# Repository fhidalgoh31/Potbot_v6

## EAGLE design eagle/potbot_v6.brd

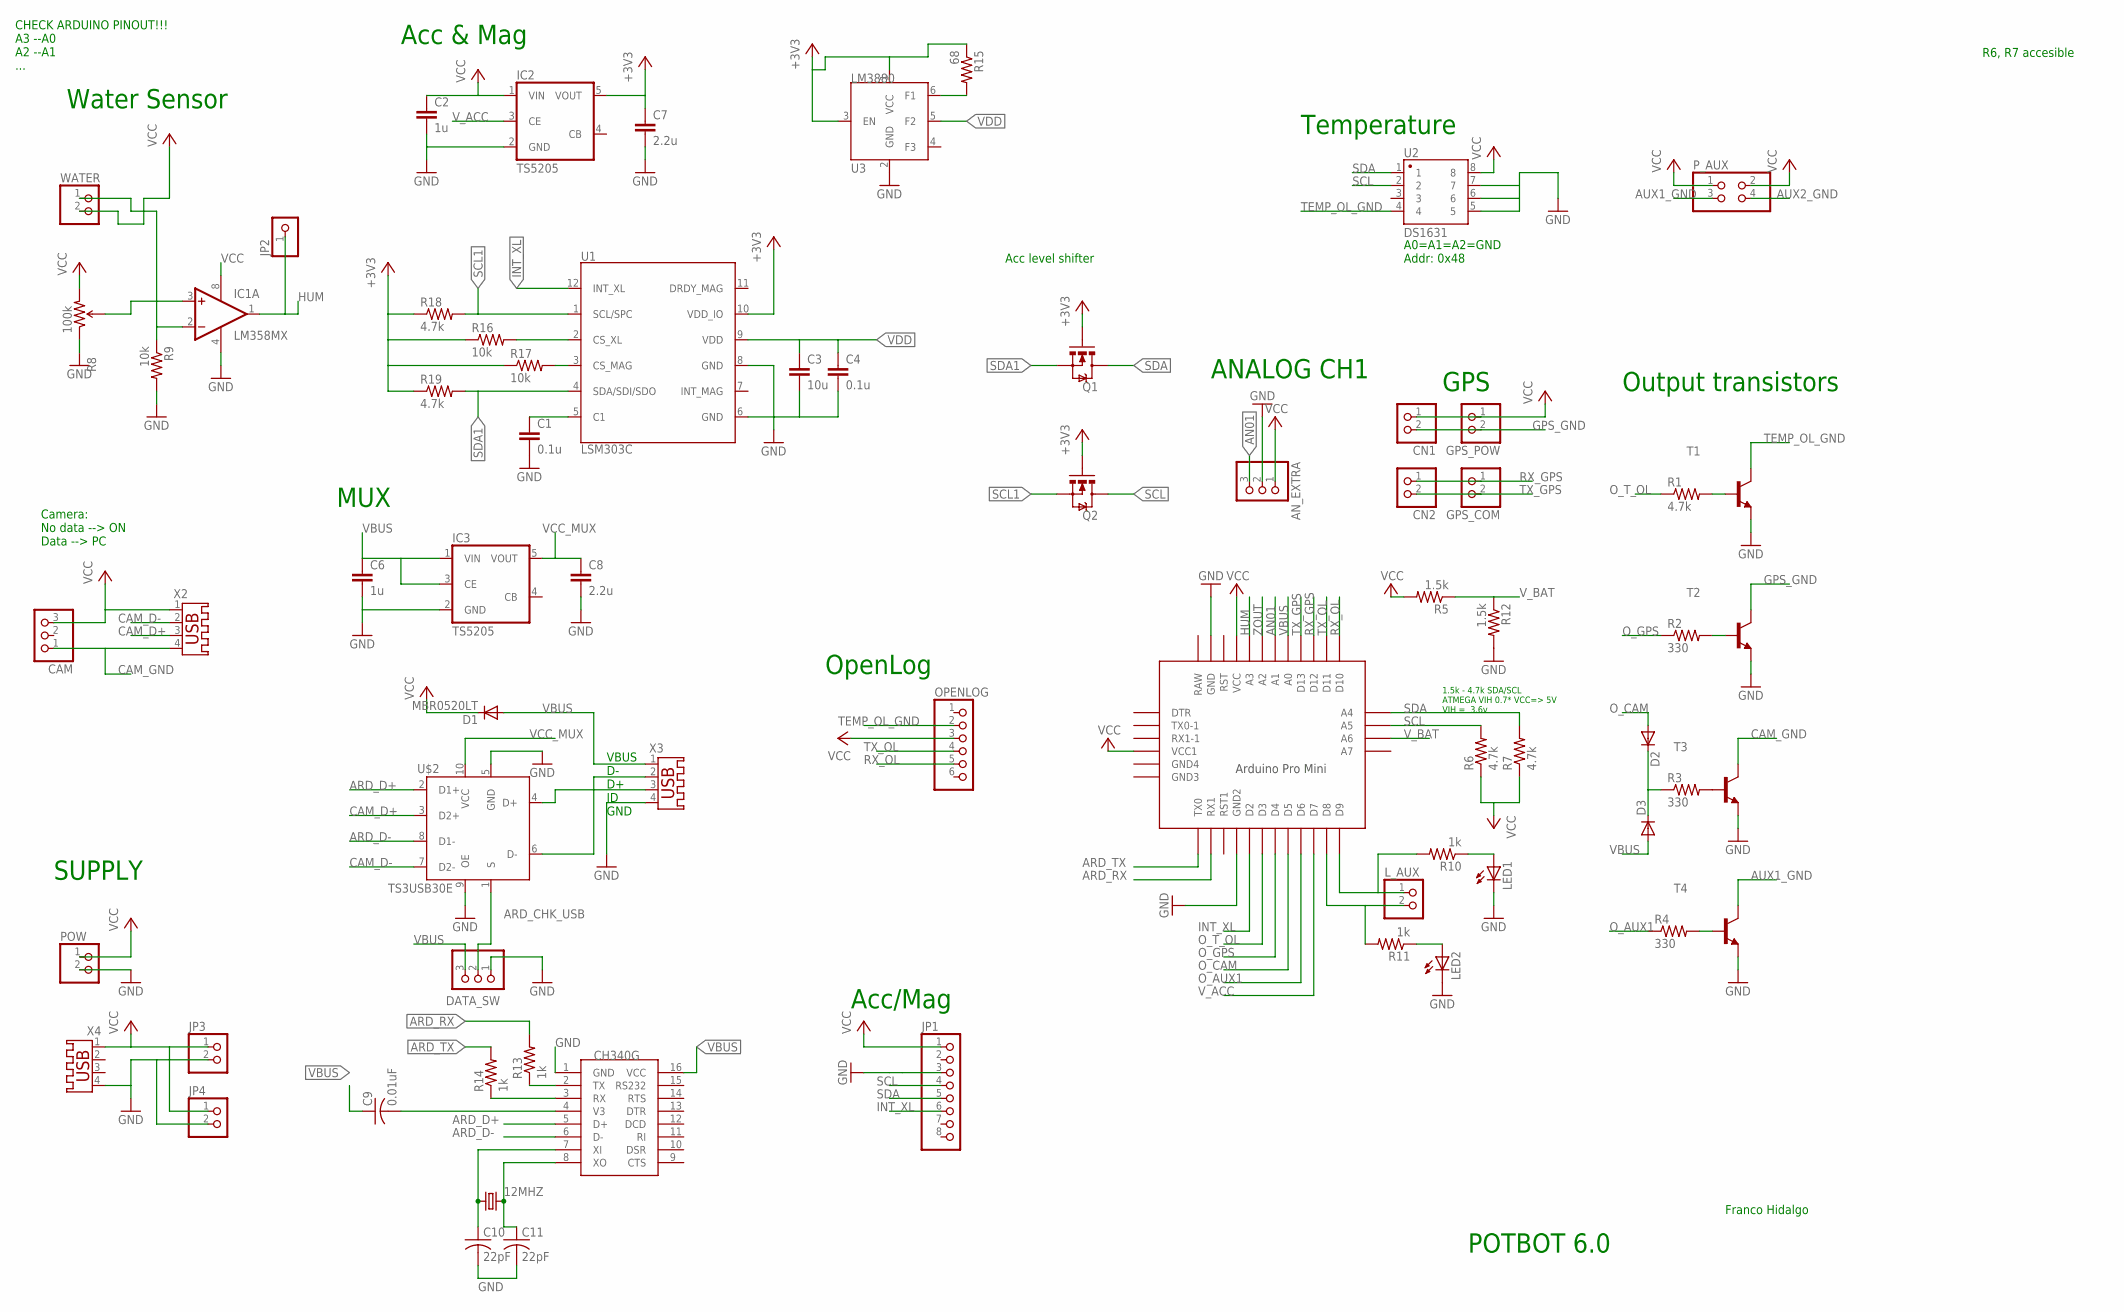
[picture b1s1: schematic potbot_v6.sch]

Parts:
12MHZ: CRYSTALSM49; SM49
AN_EXTRA: PINHD-1X3; 1X03
ARDUINO: PRO-MINI-2
C1, C4: 0.1u; C1206
C2, C6: 1u; C1206
C3: 10u; C1206
C7, C8: 2.2u; C1206
C9: 0.01uF; C1206
C10, C11: 22pF; C1206
CAM: PINHD-1X3; 1X03
CN1, CN2: JST_2PIN-THM; JST-PH-2-THM
D1, D2, D3: MBR0520LT; SOD123
DATA_SW: PINHD-1X3; 1X03
GPS_COM: JST_2PIN-SMT; JST-PH-2-SMT
GPS_POW: JST_2PIN-SMT; JST-PH-2-SMT
IC1: LM358MX; SO08
IC2, IC3: TS5205; SOT25
JP1: PINHD-1X8CLEANBIG; 1X08-CLEANBIG
JP2: PINHD-1X1; 1X01
JP3, JP4: PINHD-1X2; 1X02
LED1, LED2: LED_ELD260; LED_LD260
L_AUX: PINHD-1X2; 1X02
OPENLOG: PINHD-1X6; 1X06
POW: PINHD-1X2; 1X02
P_AUX: PINHD-2X2; 2X02
Q1, Q2: MOSFET-NCHANNELAO3404A; SOT23-3
R1, R6, R7, R18, R19: 4.7k; M1206
R2, R3, R4: 330; M1206
R5, R12: 1.5k; M1206
R8: 100k; TRIMPOT-3MM
R9, R16, R17: 10k; M1206
R10, R11, R13, R14: 1k; M1206
R15: 68; M1206
T1, T2, T3, T4: BC817-25LT1-NPN-SOT23-BEC; SOT23-BEC
U1: LSM303C; LGA-12
U2: DS1631; SO08-UNIVERSAL
U3: LM3880; SOT23-6
U$2: TS3USB30E; VSSOP8
U$4: CH340G; SOIC16
WATER: PINHD-1X2; 1X02
X2, X3, X4: USB-A003

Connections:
+3V3: C7.1, IC2.5 (VOUT), Q1.1 (G), Q2.1 (G), R15.1, R16.1, R17.1, R18.1, R19.1, U1.10 (VDD_IO), U3.1 (VCC), U3.3 (EN)
AN01: AN_EXTRA.3, ARDUINO.A1
ARD_CHK_USB: DATA_SW.2, U$2.1 (S)
ARD_D+: U$2.2 (D1+), U$4.5 (D+)
ARD_D-: U$2.8 (D1-), U$4.6 (D-)
ARD_RX: ARDUINO.RX1, R13.2
ARD_TX: ARDUINO.TX0, R14.2
AUX1_GND: P_AUX.3, T4.C
AUX2_GND: P_AUX.4
CAM_D+: U$2.3 (D2+), X2.3
CAM_D-: U$2.7 (D2-), X2.2
CAM_GND: CAM.1, T3.C, X2.4
GND: AN_EXTRA.2, ARDUINO.GND, ARDUINO.GND1 (GND2), C1.2, C2.2, C3.2, C4.2, C6.2, C7.2, C8.2, C10.2, C11.2, DATA_SW.1, IC1.4 (V-), IC2.2 (GND), IC3.2 (GND), JP1.3, JP3.2, JP4.2, LED1.K (C), LED2.K (C), POW.2, R8.1 (CCW), R9.2, R12.2, T1.E, T2.E, T3.E, T4.E, U1.6 (GND), U1.8 (GND), U2.5, U2.6, U2.7, U3.2 (GND), U$2.5 (GND), U$2.9 (OE), U$4.1 (GND), X3.4, X4.4
GPS_GND: CN1.2 (1), GPS_POW.2 (1), T2.C
HUM: ARDUINO.A3, IC1.1 (OUT), JP2.1
INT_XL: ARDUINO.D2, JP1.6, U1.12 (INT_XL)
unnamed: 12MHZ.1, C10.1, U$4.7 (XI)
unnamed: IC1.2 (-IN), R9.1, WATER.1
unnamed: IC1.3 (+IN), R8.2 (WIPER)
unnamed: R1.2, T1.B
unnamed: 12MHZ.2, C11.1, U$4.8 (XO)
unnamed: R3.2, T3.B
unnamed: R2.2, T2.B
unnamed: C9.2, U$4.4 (V3)
unnamed: R4.2, T4.B
unnamed: R13.1, U$4.2 (TX)
unnamed: ARDUINO.D9, L_AUX.1, R10.2
unnamed: LED1.A, R10.1
unnamed: U$2.4 (D+), X3.3
unnamed: U$2.6 (D-), X3.2
unnamed: LED2.A, R11.1
unnamed: ARDUINO.D8, L_AUX.2, R11.2
unnamed: D2.C, D3.C, R3.1
unnamed: R14.1, U$4.3 (RX)
unnamed: C1.1, U1.5 (C1)
unnamed: R16.2, U1.2 (CS_XL)
unnamed: R15.2, U3.6 (F1)
unnamed: R17.2, U1.3 (CS_MAG)
O_AUX1: ARDUINO.D6, R4.1
O_CAM: ARDUINO.D5, D2.A
O_GPS: ARDUINO.D4, R2.1
O_T_OL: ARDUINO.D3, R1.1
RX_GPS: ARDUINO.D12, CN2.1 (2), GPS_COM.1 (2)
RX_OL: ARDUINO.D10, OPENLOG.5
SCL: ARDUINO.A5, JP1.4, Q2.3 (D), R6.2, U2.2
SCL1: Q2.2 (S), R18.2, U1.1 (SCL/SPC)
SDA: ARDUINO.A4, JP1.5, Q1.3 (D), R7.2, U2.1
SDA1: Q1.2 (S), R19.2, U1.4 (SDA/SDI/SDO)
TEMP_OL_GND: OPENLOG.2, T1.C, U2.4
TX_GPS: ARDUINO.D13, CN2.2 (1), GPS_COM.2 (1)
TX_OL: ARDUINO.D11, OPENLOG.4
VBUS: ARDUINO.A0, C6.1, C9.1, D1.A, D3.A, DATA_SW.3, IC3.1 (VIN), IC3.3 (CE), U$4.16 (VCC), X3.1
VCC: AN_EXTRA.1, ARDUINO.VCC, ARDUINO.VCC1, C2.1, CAM.3, CN1.1 (2), D1.C, GPS_POW.1 (2), IC1.8 (V+), IC2.1 (VIN), JP1.1, JP3.1, JP4.1, OPENLOG.3, POW.1, P_AUX.1, P_AUX.2, R5.2, R6.1, R7.1, R8.3 (CW), U2.8, WATER.2, X2.1, X4.1
VCC_MUX: C8.1, IC3.5 (VOUT), U$2.10 (VCC)
VDD: C3.1, C4.1, U1.9 (VDD), U3.5 (F2)
V_ACC: ARDUINO.D7, IC2.3 (CE)
V_BAT: ARDUINO.A6, R5.1, R12.1
ZOUT: ARDUINO.A2

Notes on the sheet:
A0=A1=A2=GND Addr: 0x48
Water Sensor
GPS
Acc & Mag
1.5k - 4.7k SDA/SCL ATMEGA VIH 0.7* VCC=> 5V VIH = 3.6v
OpenLog
SUPPLY
MUX
VBUS D- D+ ID GND
Output transistors
Franco Hidalgo
POTBOT 6.0
Camera: No data --> ON Data --> PC
Temperature
Acc level shifter
ANALOG CH1
Acc/Mag
R6, R7 accesible
CHECK ARDUINO PINOUT!!! A3 --A0 A2 --A1 ...

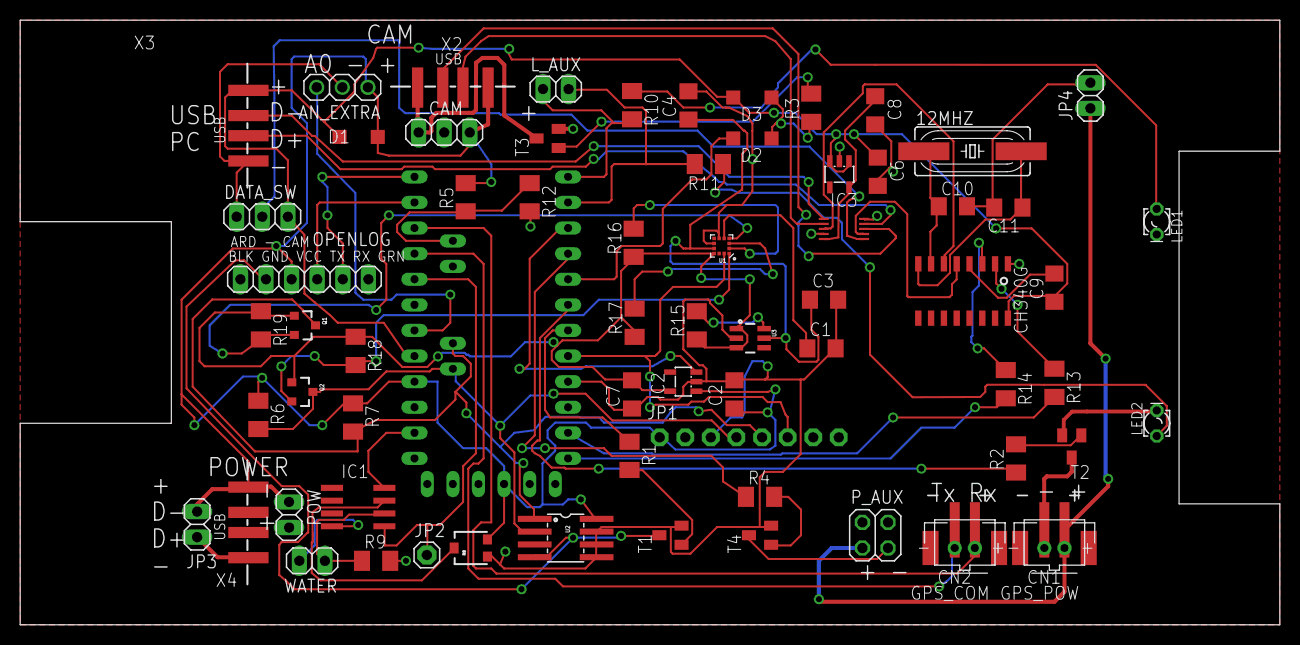
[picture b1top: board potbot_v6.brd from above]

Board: 2 copper layers, 125.0 x 60.0 mm, 69 parts (0 on the bottom side), 56 nets.

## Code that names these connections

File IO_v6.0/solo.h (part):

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#define SW_GPS  4
#define SW_CAM  5
#define VI_ACC  A1
#define TX_GPS  13
#define RX_GPS  12
#define RX_OL  11
#define TX_OL  10
#define LED  13
#define I_HUM  A3
#define temp_add 72
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
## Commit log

2016-12-06 :space_invader: Added .gitattributes & .gitignore files
2016-12-06 Potbot
    POTBOT
2016-12-08 Potbot Files
    avrdude and hex files for release versions
2017-01-27 Program too big
    Program too big, need to free memory.
    Magnetometer needed
2017-02-10 interrupt
    working with interrupts TODO: Change logic --> wet switch

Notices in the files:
parts and their libraries:
SparkFun-Electromechanical: Licensing: Creative Commons ShareAlike 4.0 International - https://creativecommons.org/licenses/by-sa/4.0
